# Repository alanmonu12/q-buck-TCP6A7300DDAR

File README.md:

View this project on [CADLAB.io](https://cadlab.io/project/30117) or [kicanvas.org](https://kicanvas.org/?repo=https%3A%2F%2Fgithub.com%2Falanmonu12%2Fq-buck-TCP6A7300DDAR%2Ftree%2Fdevelop). 

# Q-Buck TCP6A7300DDAR EVAL BOARD MX <!-- omit in toc -->

Una placa de evaluación Open Source Hardware (OSHW) diseñada para probar y caracterizar el convertidor Buck síncrono TCP6A7300DDAR, un circuito integrado diseñado en México por QSM Semiconductores. Esta placa está pensada como un primer paso para validar el comportamiento térmico, la estabilidad del lazo de control y la eficiencia del IC bajo  condiciones reales, con miras a integrarlo en proyectos educativos e industriales más grandes.

## Tabla de Contenido <!-- omit in toc -->

- [Características del IC (TCP6A7300DDAR)](#características-del-ic-tcp6a7300ddar)
- [Diseño Orientado a la Validación (Design for Testability)](#diseño-orientado-a-la-validación-design-for-testability)
- [Ecuaciones y Diseño Preliminar](#ecuaciones-y-diseño-preliminar)
- [Lista de Materiales (BOM) y Consideraciones de Ensamblaje](#lista-de-materiales-bom-y-consideraciones-de-ensamblaje)
- [Especificaciones de Manufactura y Stackup](#especificaciones-de-manufactura-y-stackup)
- [Estado del Proyecto](#estado-del-proyecto)
- [Referencias y Documentación](#referencias-y-documentación)
- [License](#license)

## Características del IC (TCP6A7300DDAR)

El núcleo de este proyecto es la evaluación en hardware del convertidor TCP6A7300DDAR, un circuito integrado diseñado y manufacturado en México. La motivación principal es impulsar la industria electrónica nacional, demostrando que es posible integrar silicio de origen local en topologías de potencia confiables.

- Voltaje de Entrada ($V_{IN}$): 3.8V a 35V
- Corriente de Salida: 3A Continuos
- Frecuencia de Conmutación: 500 kHz
- Voltaje de Referencia ($V_{REF}$): 0.8V
- Topología: Step-Down (Buck) Síncrono
- Empaquetado: SOP-8 con *Exposed Pad*

<p align="center">
  
  <br>
  <em>Topología básica de aplicación del IC.</em>
</p>

## Diseño Orientado a la Validación (Design for Testability)

Esta tarjeta fue pensada para ir mucho más allá de ser una simple implementación de referencia del IC TCP6A7300DDAR. Su arquitectura está pensada como un entorno de laboratorio para enseñar, experimentar y comprender a fondo los fenómenos dinámicos y electromagnéticos que rigen a las fuentes conmutadas. 

Para lograr esto, la placa integra características específicas de validación:

- **Análisis de Estabilidad y Lazo de Control:** Cuenta con un punto de inyección de señal. Esto permite aislar el lazo de retroalimentación en corriente alterna (AC) para inyectar pequeña señal y extraer el Diagrama de Bode utilizando instrumentos como el Analog Discovery 3, facilitando el estudio práctico del Margen de Fase y Ganancia.
- **Filtro Pi para Mitigación EMI:** Se integraron footprints opcionales a la entrada para conformar un filtro Pi pasivo (dos capacitores cerámicos separados por un Ferrite Bead o inductor de alta frecuencia). Esto permite a los ingenieros evaluar empíricamente la atenuación del ruido conducido, entender el filtrado de armónicos y analizar cómo la impedancia de entrada afecta la estabilidad del convertidor. 
- **Flexibilidad de Operación:** Diseñada por defecto para entregar un riel estable de 5V, incluye opciones de montaje para un potenciómetro de ajuste, esto facilita la ejecución de barridos de voltaje.

<p align="center">
  
  <br>
  <em> Diagrama de referencia (TI) para la inyección de pequeña señal AC en el lazo de retroalimentación. La placa de evaluación integra este arreglo físico mediante el resistor de inyección flotante y conectores SMD dedicados.</em>
</p>

## Ecuaciones y Diseño Preliminar

El circuito actual está calculado para un escenario típico de reducción de voltaje (ej. batería de $12V/24V$ a $5V$ para lógica).

**Parámetros de Diseño:**

- $V_{IN(max)} = 35V$
- $V_{OUT} = 5V$
- $I_{OUT} = 1A$
- $f_{sw} = 500 kHz$

**1. Lazo de Retroalimentación (Feedback)**

El divisor de voltaje se calcula basándose en la referencia interna de 0.8V. Asignando $R_2 = 10k\Omega$:

$$R_1 = R_2 \left( \frac{V_{OUT}}{V_{REF}} - 1 \right)$$
$$R_1 = 10k\Omega \left( \frac{5V}{0.8V} - 1 \right) = 52.5 k\Omega$$

   >[!NOTE]
   >
   > En el esquemático se utiliza el valor comercial estándar más cercano de $56k\Omega$, lo que resulta en un $V_{OUT}$ real aproximado de $5.28V$.

**2. Cálculo del Inductor ($L$)**

Se asume un rizado de corriente ($\Delta I_L$) del 30% de la corriente de salida nominal ($I_{OUT} = 2A$), resultando en $\Delta I_L = 600mA$.

$$L = \frac{V_{OUT} (V_{IN} - V_{OUT})}{V_{IN} \cdot f_{sw} \cdot \Delta I_L}$$
$$L = \frac{5V (35V - 5V)}{35V \cdot 500kHz \cdot 600mA} = 14.28 \mu H$$

   >[!NOTE]
   >
   > Se elige un valor comercial estándar de $10 \mu H$, lo que aumentará ligeramente el rizado de corriente, pero mejorará la respuesta transitoria.

**3. Capacitor de Salida ($C_{OUT}$)**

Para mantener un rizado de voltaje en la salida ($\Delta V_{OUT}$) menor a $20mV$:

$$C_{OUT} = \frac{\Delta I_L}{8 \cdot f_{sw} \cdot \Delta V_{OUT}}$$
$$C_{OUT} = \frac{600mA}{8 \cdot 500kHz \cdot 20mV} = 7.5 \mu F$$

   >[!NOTE]
   >
   > Se utiliza un valor estándar de $10 \mu F$ con un capacitor cerámico multicapa.

## Lista de Materiales (BOM) y Consideraciones de Ensamblaje

Este prototipo fue diseñado bajo una filosofía de **"tropicalización" y rápida iteración**. Todos los componentes pasivos seleccionados son de montaje superficial (SMD tamaño 0805) y están restringidos a números de parte comerciales que se pueden adquirir inmediatamente en el mercado local mexicano (ej. Unit Electronics), evitando tiempos de importación.

Reference|	Qty|	Part number|	Value|	DNP|	Footprint|	Supplier |
| :--- | :--- | :--- | :--- | :--- | :--- | :--- |
C1, C4, C5|	3|	CC0805KRX7R9BB104|	0.1uF|	|	0805_2012Metric|	[Link](https://uelectronics.com/producto/cc0805krx7r9bb104-capacitor-ceramico-0805-100nf-50v/) |
C2|	1|	UMK212ABJ225KG-T|	2.2uF|	|	0805_2012Metric|	[Link](https://uelectronics.com/producto/umk212abj225kg-t-capacitor-ceramico-0805-2-2uf-50v/) |
C3|	1|	TMK212BBJ106KG-T|	10uF|	| 0805_2012Metric|	[Link](https://uelectronics.com/producto/tmk212bbj106kg-t-capacitor-ceramico-0805-10uf-25v/) |
C6|	1|	CL21C101JBANNNC|	100pF|	|	0805_2012Metric|	[Link](https://uelectronics.com/producto/capacitor-ceramico-0805-100pf-50v-cl21c101jbannnc/) |
C7, C8|	2|	CL31B106KBHNNNE|	10uF|	DNP|	1206_3216Metric|	[Link](https://uelectronics.com/producto/cl31b106kbhnnne-capacitor-ceramico-1206-10uf-50v/) |
C9, C10|	2|	CC0805KRX7R9BB104|	0.1uF|	DNP|	0805_2012Metric|	[Link](https://uelectronics.com/producto/cc0805krx7r9bb104-capacitor-ceramico-0805-100nf-50v/) |
FB1|	1|	DNP|	DNP|	DNP|	0805_2012Metric|	|
J1, J2|	2|	691322310002|	691322310002|	|	TH |	|
J3|	1|	BM02B-SRSS-TB LFSN|	BM02B-SRSS-TB LFSN|	|	SMD|	[Link](https://uelectronics.com/producto/conectores-sh1-0mm-verticales/) |
L1|	1|	SWPA6020S100MT|	10uH|	|	IND_SWPA6020S_SNL|	[Link](https://uelectronics.com/producto/indutor-de-ferrita-10uh-1-15a-slf0403-100mtt/?srsltid=AfmBOooOqTnwMiDMHeULKfOL0IrJwGuaZDGph-w8FWtPsK44g1PSEBvX) |
R1|	1|	RC0805JR-0756KL|	56K|	|	0805_2012Metric|	[Link](https://uelectronics.com/producto/resistor-56k-ohm-1-8w-smd-0805-rs-05k6802ft/) |
R2|	1|	0805W8F1002T5E|	10K|	|	0805_2012Metric|	[Link](https://uelectronics.com/producto/resistor-10k-ohm-1-8w-smd-0805-0805w8f2202t5e/?srsltid=AfmBOooCz4q4fAaZYE-h_EAgrFxCbTD7xwc4qPOiGFs1Ch7HIS5tJjUF) |
R3|	1|	RTT05000JTP|	0R|	|	0805_2012Metric|	[Link](https://uelectronics.com/producto/resistor-0-ohm-1-8w-smd-0805-rtt05000jtp/) |
R4|	1|	TC33X-2-103E|	100K|	DNP|	SMD |	[Link](https://uelectronics.com/producto/trimpot-smd-10k-ohm-3x3-8mm-tc33x-2-103e/) |
U1|	1|	TCP6A7300DDAR|	TCP6A7300DDAR|	|	SOIC-8-1EP_ThermalVias|	|

> [!NOTE]
> 
> Los footprints marcados como **DNP** (Do Not Populate) en el esquemático, se dejaron intencionalmente vacíos para permitir soldar componentes adicionales durante la fase de validación en banco de pruebas.

## Especificaciones de Manufactura y Stackup

Para obtener buenos resultados térmicos y electromagnéticos, la tarjeta fue diseñada utilizando un perfil de manufactura de 4 capas estándar. El objetivo es que cualquier ingeniero pueda mandar a fabricar este diseño en casas ensambladoras de bajo costo (como JLCPCB o PCBWay) sin tener en cargos extras por procesos avanzados.

**Características Físicas de la Placa:**

* **Dimensiones:** 45.0 mm x 30.0 mm.
* **Grosor Total:** 1.6 mm.
* **Acabado Superficial:** HAL Lead-Free (HASL libre de plomo RoHS).
* **Reglas de Diseño (DRC):** Ruteo robusto con pista/separación mínima de 0.2 mm (aprox. 8 mils) y diámetro de perforación (vías) mínimo de 0.3 mm. 

**Análisis del Stackup (Cobre de 1 oz):**

* **Capa 1 (Top) - Señal y Potencia:** Aloja todos los componentes SMD, el "Hot Loop" y el nodo SW.
* **Capa 2 (In1) - Plano de Tierra Sólido (GND):** Actúa como escudo de Faraday y ruta de retorno de baja impedancia.
* **Capa 3 (In2) - Plano de Tierra (GND):** aporta masa térmica adicional para la disipación del IC. Utilizada para llevar la señal sensible de retroalimentación (Feedback) protegida entre dos planos de tierra.
* **Capa 4 (Bottom) - Ruteo y Planos Auxiliares:**  Utilizada para llevar la señal sensible de retroalimentación (Feedback).

## Estado del Proyecto

- [x] Cálculo de componentes pasivos.
- [x] Captura del Esquemático (KiCad).
- [x] Diseño del PCB (Layout y consideraciones térmicas).
- [ ] Ensamble del primer prototipo.
- [ ] Pruebas de caracterización y respuesta en frecuencia (FRA).

## Referencias y Documentación

[1]: [Basic Calculation of a Buck Converter's Power Stage (SLVA477B)](https://www.ti.com/lit/an/slva477b/slva477b.pdf)

[2]: [How to Measure the Loop Transfer Function of Power Supplies (AN-1889 / SNVA364A)](https://www.ti.com/lit/an/snva364a/snva364a.pdf)

[3]: [Analysis and Design of Input Filter for DC-DC Circuit (SNVA801)](https://www.ti.com/lit/pdf/snva801)

[4]: [Design a Second-stage Filter for Sensitive Applications (SSZT824)](https://www.ti.com/lit/pdf/sszt824)

[5]: [How to select input capacitors for a buck converter](https://www.ti.com/lit/an/slyt670/slyt670.pdf)

[6]: [Improve High-Current DC/DC Regulator EMI Performance for Free With Optimized Power Stage Layout](https://www.ti.com/lit/ab/snva803/snva803.pdf?ts=1772697173603)

[7]: [DC-DC PCB Layout Design for EMC](https://www.diodes.com/assets/App-Note-Files/AN1191-DC-DC-PCB-Layout-Design-for-EMC.pdf)

## License

This project is licensed under the CC BY-NC-SA 4.0 License. See the LICENSE file for details.

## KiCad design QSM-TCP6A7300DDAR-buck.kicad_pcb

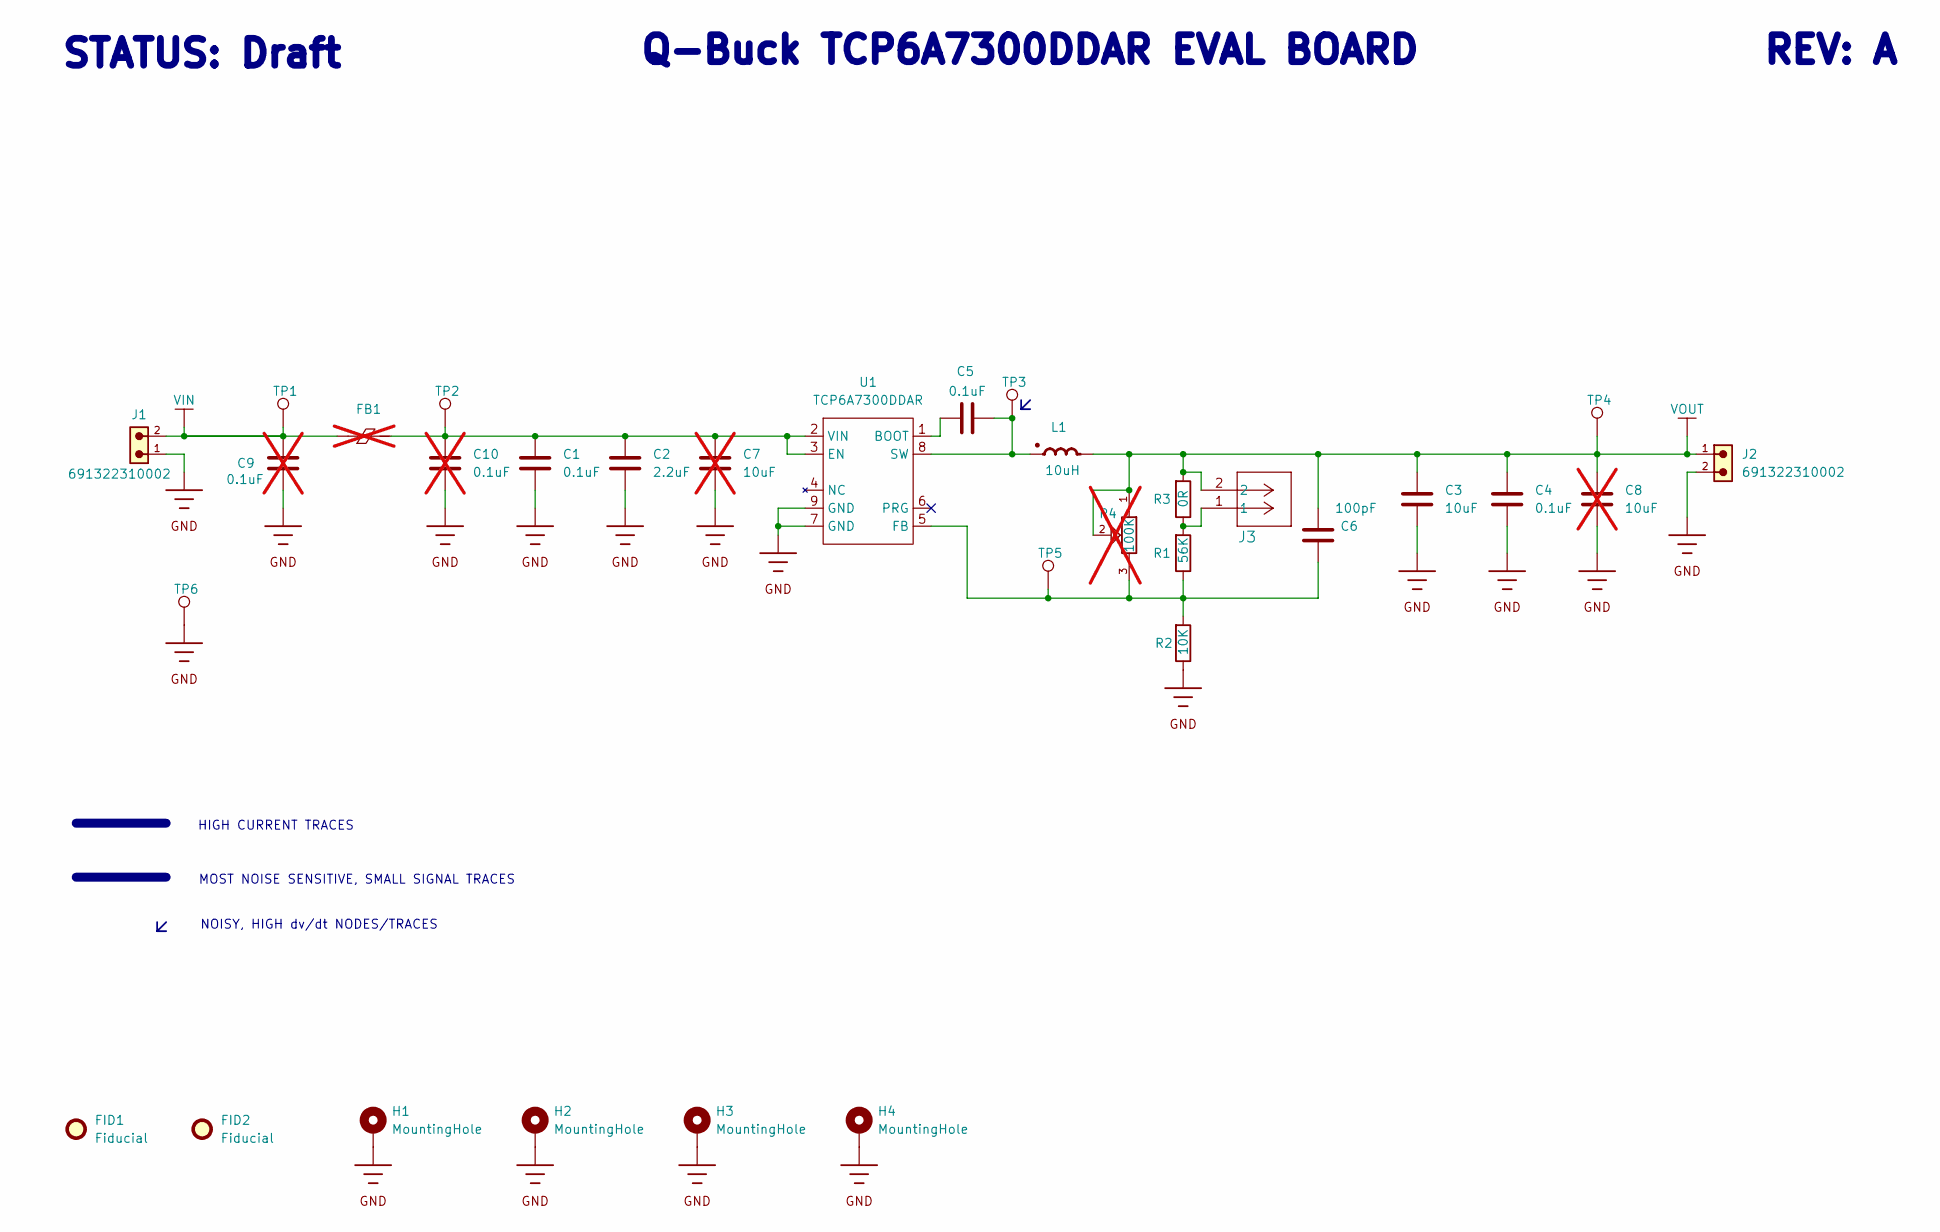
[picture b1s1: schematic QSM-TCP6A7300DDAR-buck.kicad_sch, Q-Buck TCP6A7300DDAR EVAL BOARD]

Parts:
C1, C4, C5: 0.1uF; C_0805_2012Metric; Tolerance ± 10%; Voltage 50V; Part number CC0805KRX7R9BB104
C2: 2.2uF; C_0805_2012Metric; Tolerance ±10%; Voltage 50V; Part number UMK212ABJ225KG-T
C3: 10uF; C_0805_2012Metric; Tolerance ±10%; Voltage 25V; Part number TMK212BBJ106KG-T
C6: 100pF; C_0805_2012Metric; Tolerance ± 5%; Voltage 50V; Part number CL21C101JBANNNC
C7, C8: 10uF; C_1206_3216Metric; Tolerance ± 10%; Voltage 50V; Part number CL31B106KBHNNNE; not fitted
C9, C10: 0.1uF; C_0805_2012Metric; Tolerance ± 10%; Voltage 50V; Part number CC0805KRX7R9BB104; not fitted
FB1: R_0805_2012Metric; not fitted
FID1, FID2: Fiducial; Fiducial_0.5mm_Mask1.5mm
H1, H2, H3, H4: MountingHole; MountingHole_3.2mm_M3_Pad_Via
J1, J2: 691322310002
J3: BM02B-SRSS-TB LFSN; BM02B-SRSS-TB_JST; Part number BM02B-SRSS-TB LFSN
L1: 10uH; IND_SWPA6020S_SNL; Tolerance ±20%; Current Rating 1.4 A; Part number SWPA6020S100MT
R1: 56K; R_0805_2012Metric; Tolerance ± 5%; Part number RC0805JR-0756KL
R2: 10K; R_0805_2012Metric; Tolerance ± 1%; Part number 0805W8F1002T5E
R3: 0R; R_0805_2012Metric; Tolerance ± 5%; Part number RTT05000JTP
R4: 100K; POT_TC33_3X3P8_BRN; Part number TC33X-2-103E; not fitted
TP1, TP2, TP3, TP4, TP5, TP6: TestPoint; TestPoint_Pad_D1.0mm
U1: TCP6A7300DDAR; SOIC-8-1EP_3.9x4.9mm_P1.27mm_EP2.29x3mm_ThermalVias

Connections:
GND: C1.2, C2.2, C3.2, C4.2, C7.2, C8.2, C9.2, C10.2, H1.1 (1_1), H2.1 (1_1), H3.1 (1_1), H4.1 (1_1), J1.1, J2.2, R2.2, TP6.1 (1_1), U1.7 (GND), U1.9 (GND)
unnamed: C3.1, C4.1, C6.1, C8.1, J2.1, J3.2, L1.2, R3.1, R4.1, R4.2, TP4.1 (1_1)
unnamed: C9.1, FB1.1, J1.2, TP1.1 (1_1)
unnamed: J3.1, R1.1, R3.2
unnamed: C5.1, U1.1 (BOOT)
unnamed: C1.1, C2.1, C7.1, C10.1, FB1.2, TP2.1 (1_1), U1.2 (VIN), U1.3 (EN)
unnamed: C6.2, R1.2, R2.1, R4.3, TP5.1 (1_1), U1.5 (FB)
unnamed: C5.2, L1.1, TP3.1 (1_1), U1.8 (SW)

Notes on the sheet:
${TITLE}
MOST NOISE SENSITIVE, SMALL SIGNAL TRACES
REV: ${REVISION}
HIGH CURRENT TRACES
STATUS: ${COMMENT1}
NOISY, HIGH dv/dt NODES/TRACES

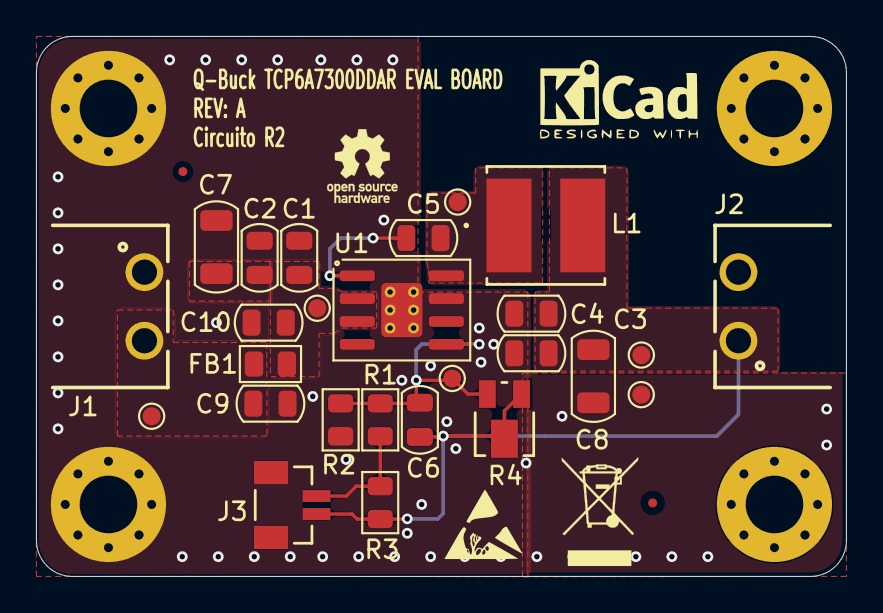
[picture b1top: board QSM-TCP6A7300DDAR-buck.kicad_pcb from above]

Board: 4 copper layers, 45.0 x 30.0 mm, 32 parts (0 on the bottom side), 8 nets.

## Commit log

2026-02-27 feat: commit inicial con esquemático del Q-Buck TCP6A7300DDAR y documentación base
    Incluye el archivo README.md con cálculos de lazo de retroalimentación, referencias bibliográficas y el esquemático preliminar en KiCad v10.
2026-02-27 docs: identificar trazos críticos en el esquemático para ruteo
    Se agregaron colores y leyendas para diferenciar las pistas de alta corriente (rojo), señales sensibles de retroalimentación (amarillo) y nodos ruidosos con alto dv/dt. Sirve como guía visual obligat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
2026-02-27 Backlink to CADLAB.io has been added.
2026-03-02 docs: agregar lista de materiales (BOM) y límites de hardware
    Se integró la tabla de componentes críticos con enlaces a proveedores locales para ensamble rápido. También se documentaron las consideraciones de derating físico: límite de corriente de 1.4A por sat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
2026-03-03 feat: agregar test points en nodos críticos y referencias de filtros EMI
    Se colocaron Test Points estratégicos en el esquemático (ej. VIN, VOUT, SW y el lazo de Feedback) para facilitar las mediciones con osciloscopio y la inyección de señal. Además, se actualizó el READM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
2026-03-04 feat(layout): [WIP] ruteo inicial de polígonos de potencia en 4 capas
    Se definió el stackup simétrico de 4 capas (SIG-GND-GND-SIG) y se realizó el floorplanning. Se trazaron los polígonos preliminares de alta corriente (VIN, SW, VOUT) en la capa Top. El ruteo de la señ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
2026-03-06 feat(hardware): optimización de hot-loops, conector de inyección de señal y actualización de docs
    Esquemático y PCB:
    - Reubicación jerárquica de capacitores de entrada y salida para minimizar el área del Hot Loop y reducir el ESL, alineado a notas de aplicación de PI.
    - Adición de conector SMD JST SH (BM02B-SRSS-TB) en paralelo a la resistencia de inyección para facilitar la medición del lazo de control (Bode Plot).
    Documentación (README):
    - Integración de 'badges' de estado y especificaciones técnicas.
    - Redacción de la justificación técnica del layout (Control EMI y Hot Loops) referenciando bibliografía de TI.
2026-03-06 chore(project): preparación para manufactura (BOM, stackup PCB y docs)
    Documentación (README):
    - Refactorización de la narrativa del proyecto enfocándose en la validación empírica y el desarrollo de la industria nacional.
    - Integración de la sección 'Design for Testability' (DFT) y justificación técnica del stackup de 4 capas.
    Layout (PCB):
    - Adición de las tablas de características de la placa y detalles del stackup (capas, grosores de FR4/Prepreg y cobre) en la capa de dibujo para referencia del fabricante.
    Proyecto y Esquemático:
2026-03-06 build(mfg): automatización de salidas de manufactura mediante Jobsets
    Integración de archivos de configuración (Jobsets) para estandarizar y automatizar la generación del paquete de producción.
    Se automatizan las siguientes salidas con reglas predefinidas:
    - Archivos Gerber (Cobre, Máscaras, Serigrafía, Bordes).
    - Archivos de taladrado Excellon (Drill files PTH/NPTH).
    - Lista de Materiales (BOM) formateada para ensamble.
    - Archivo de Posición de Componentes (CPL / Pick and Place) para procesos de Pick & Place SMD.
